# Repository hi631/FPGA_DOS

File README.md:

Build a DOS machine with FPGA.

Move "[next186](https://opencores.org/projects/next186_soc_pc)" on the board cut by CNC.
<br> Even if the software is existing and reliable, there is no guarantee that the hardware will work, so take the following steps.
<br> Step-1 Connect memory, IO, etc. to a commercially available FPGA (xc6lx9) board, move it with CP / M, and check the hardware operation.
<br> * Even with CP / M, the main memory is not static but DRAM.
<br> However, since burst access is not performed, defect verification is easy.
<br> Step-2 Operate as a DOS system on the above hardware.
<br> * Actually, the memory (DRAM) did not work properly, and I stepped on here for several months. How it works.
<br> Step-3 Create a printed circuit board with CNC, first verify the operation of the hardware with CP / M, and then operate the DOS system.
<br>
<br> Describe the hardware / software to be used for reference.
<br> [lx9-Step-1-io] Expansion platform used in Steps 1 and 2. It is operated by piercing a commercially available board (XC6SLX9 Mini Board).
<br> [MAIN-BOARD] Motherboard with FPGA and DRAM.
<br> [PMOD-IO] A board that connects the SD card and keyboard. Stick in MAIN-BOARD.
<br> [PMOD-VGA6] VGA display output. Stick in MAIN-BOARD.
<br> [lx9-Step1-CPM80] Circuit for operating CP / M (verilog)
<br> [lx9-Next186_SoC] Circuit for operating DOS (verilog)
<br>「[SD2G_Dos_F.zip] free MS-DOS SD-image

<br> For details, see "[Qiita](https://qiita.com/hi631/items/e8e0db06a52938b57632)".

<br>
<br> Part 2: I will run DOS using the CYC1000 board (cut-out edition)

<br> #Move on breadboard
<br> Just stab the CYC1000 into the breadboard and stab the IO in the same way. Only this.
<br> IO is a board, but there is no problem with wiring on the board.
<br> The wiring is the same as "[Board] ", so please refer to that.
<br> #Move with a compact board.
<br> A compact board with breadboard wiring cut by CNC. That's all.
<br> [Board made with eagle] max1000_eagle
<br> #soft
<br> The breadboard and board are the same software.
<br> However, I just changed the pin layout of next186.
<br> [Software to write to FPGA] max1000_Next186_SoC
<br> [Boot disk image] SD2G_Dos_F.zip

<br> For details, see "[Qiita](https://qiita.com/hi631/items/d948d38c25a411d28f2b)".

<br>DOSマシンをFPGAで作る。

<br>　「[next186](https://opencores.org/projects/next186_soc_pc)」をCNCで切削した基板上で動かす。
<br>　ソフトが既存で信頼できても、ハードが動作する保証は無いので、次のようなステップを踏む。
<br>　Step-1　市販FPGA(xc6lx9)基板にメモリ、IO等を繋ぎ、CP/Mで動かしハード動作を確認。
<br>　　　　　※CP/Mでも、メインメモリはスタティックでは無くDRAMで構成する。
<br>　　　　　　但し、バーストアクセスは行わないので、不具合検証はやり易い。
<br>　Step-2　上記ハード上で、DOSシステムとして動作させる。
<br>　　　　　※実際の所、メモリ(DRAM)が正常に動作せず、ここで数か月足踏みした。しくしく。
<br>　Step-3　CNCでプリント基板を作成し、先にCP/Mでハードの動作検証を行い、その後DOSシステムを動作させる。
<br>
<br>　使用するハード/ソフトを参考まで記載。
<br>　　[lx9-Step-1-io]　　Step-1,2で使用する拡張基盤。市販基板(XC6SLX9 Mini Board)に刺して動作させる。
<br>
<br>　　[MAIN-BOARD]　FPGAとDRAMを乗せた基盤。
<br>
<br>　　[PMOD-IO]　　SDカードとキーボードを繋ぐ基板。MAIN-BOARDに刺す。
<br>　　[PMOD-VGA6]　VGAディスプレイ出力。MAIN-BOARDに刺す。
<br>
<br>　　[lx9-Step1-CPM80]　CP/Mを動作させる為の回路(verilog)
<br>　　[lx9-Next186_SoC]　DOSを動作させるための回路(verilog)
<br>「[SD2G_Dos_F.zip](https://github.com/hi631/FPGA_DOS/blob/master/SD2G_Dos_F.zip)　free MS-DOS SDイメージ

<br>詳細は　「[Ｑｉｉｔａ](https://qiita.com/hi631/items/e8e0db06a52938b57632)」を見てください。

<br>その２：CYC1000ボードを使ってDOSを動かすぞ(手抜き編)
　
<br>#ブレッドボード上で動かす
<br>　CYC1000をブレッドボードに刺し、同様にＩＯを刺すだけ。これだけです。
<br>　ＩＯは基板にしたが、ボード上で配線でもなんら問題ない。
<br>　配線は「[基板]((https://github.com/hi631/FPGA_DOS/tree/master/max1000_eagle))」と同じなので、そちらを参照してね。
<br>

<br>#コンパクトな基板で動かす。
<br>　ブレッドボードの配線を、CNCで切削したコンパクトな基板。それだけです。
<br>　[eagleで作製した基板](https://github.com/hi631/FPGA_DOS/tree/master/max1000_eagle)
<br>

<br>#ソフト
<br>　ブレッドボード、基板共に同一ソフトです。
<br>　と言っても、next186のピン配置を変えただけですが。
<br>　[ＦＰＧＡに書き込むソフト](https://github.com/hi631/FPGA_DOS/tree/master/max1000_Next186_SoC)
<br>　[ブートディスクのイメージ](https://github.com/hi631/FPGA_DOS/blob/master/SD2G_Dos_F.zip)

<br>詳細は　「[Ｑｉｉｔａ](https://qiita.com/hi631/items/d948d38c25a411d28f2b)」を見てください。

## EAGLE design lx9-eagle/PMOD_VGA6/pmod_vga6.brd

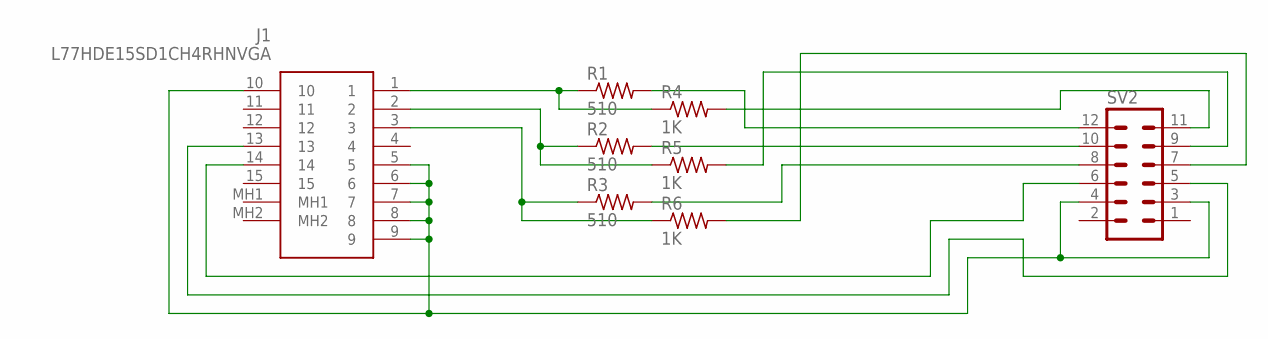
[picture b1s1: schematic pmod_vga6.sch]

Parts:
J1: L77HDE15SD1CH4RHNVGA
R1, R2, R3: 510; R0805
R4, R5, R6: 1K; R0805
SV2: MA06-2

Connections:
unnamed: J1.1, R1.1, R4.1
unnamed: J1.2, R2.1, R5.1
unnamed: J1.3, R3.1, R6.1
unnamed: R1.2, SV2.12
unnamed: R4.2, SV2.11
unnamed: R2.2, SV2.10
unnamed: R5.2, SV2.9
unnamed: R3.2, SV2.8
unnamed: R6.2, SV2.7
unnamed: J1.14, SV2.6
unnamed: J1.13, SV2.5
unnamed: J1.5, J1.6, J1.7, J1.8, J1.9, J1.10, SV2.3, SV2.4

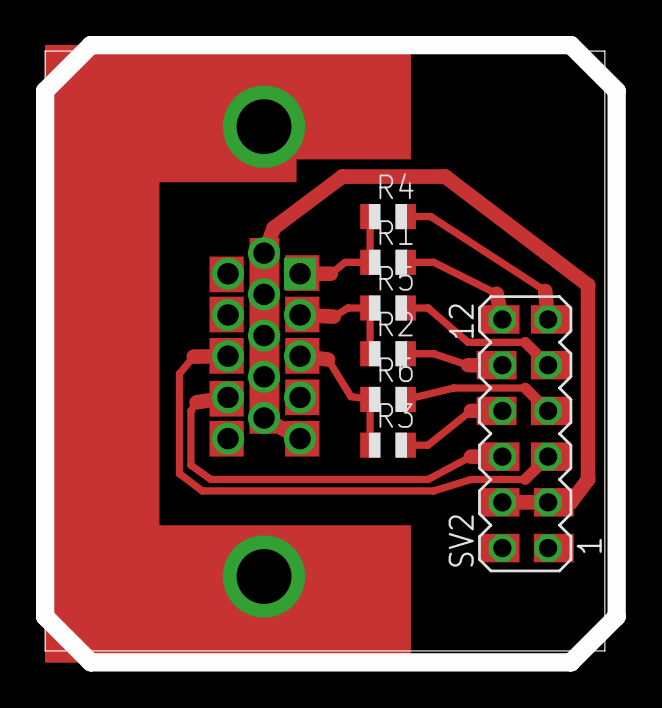
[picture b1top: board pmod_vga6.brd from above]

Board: 2 copper layers, 31.8 x 34.3 mm, 8 parts (1 on the bottom side), 12 nets.

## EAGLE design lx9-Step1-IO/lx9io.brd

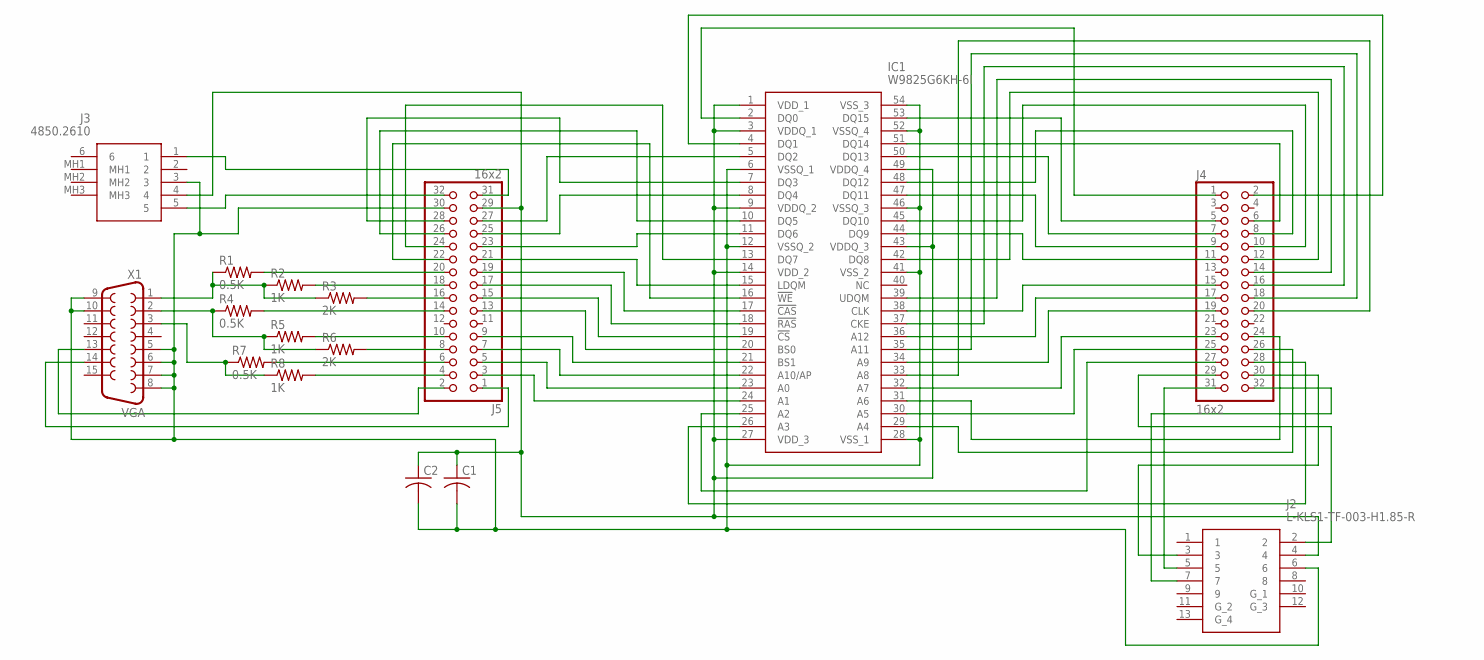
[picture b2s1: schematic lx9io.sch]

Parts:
C1, C2: C-USC0805; C0805
IC1: W9825G6KH-6I; SOP80P1176X120-54N
J2: L-KLS1-TF-003-H1.85-R
J3: 4850.2610; 48502610
J4, J5: 16x2; 2X16
R1, R4, R7: 0.5K; M0805
R2, R5, R8: 1K; M0805
R3, R6: 2K; M0805
X1: VGA; HDF15H

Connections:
unnamed: IC1.50 (DQ13), J4.7
unnamed: IC1.2 (DQ0), J4.1
unnamed: C1.2, C2.2, IC1.6 (VSSQ_1), IC1.12 (VSSQ_2), IC1.28 (VSS_1), IC1.41 (VSS_2), IC1.46 (VSSQ_3), IC1.52 (VSSQ_4), IC1.54 (VSS_3), J2.6, J3.3, J5.30, X1.5, X1.6, X1.7, X1.8, X1.9, X1.10
unnamed: IC1.53 (DQ15), J4.5
unnamed: IC1.47 (DQ11), J4.9
unnamed: IC1.44 (DQ9), J4.11
unnamed: IC1.38 (CLK), J4.15
unnamed: IC1.36 (A12), J4.17
unnamed: IC1.34 (A9), J4.19
unnamed: IC1.32 (A7), J4.23
unnamed: IC1.30 (A5), J4.25
unnamed: IC1.51 (DQ14), J4.6
unnamed: IC1.48 (DQ12), J4.8
unnamed: IC1.45 (DQ10), J4.10
unnamed: IC1.42 (DQ8), J4.12
unnamed: IC1.39 (UDQM), J4.14
unnamed: IC1.37 (CKE), J4.16
unnamed: IC1.35 (A11), J4.18
unnamed: IC1.33 (A8), J4.20
unnamed: IC1.31 (A6), J4.24
unnamed: IC1.29 (A4), J4.26
unnamed: IC1.4 (DQ1), J4.2
unnamed: IC1.25 (A2), J4.27
unnamed: IC1.26 (A3), J4.28
unnamed: IC1.10 (DQ5), J5.26
unnamed: IC1.5 (DQ2), J5.27
unnamed: IC1.7 (DQ3), J5.28
unnamed: IC1.8 (DQ4), J5.25
unnamed: IC1.11 (DQ6), J5.23
unnamed: IC1.13 (DQ7), J5.24
unnamed: IC1.15 (LDQM), J5.21
unnamed: IC1.16 (!WE), J5.22
unnamed: IC1.17 (!CAS), J5.19
unnamed: IC1.18 (!RAS), J5.17
unnamed: IC1.19 (!CS), J5.15
unnamed: IC1.20 (BS0), J5.13
unnamed: IC1.21 (BS1), J5.9
unnamed: IC1.22 (A10/AP), J5.7
unnamed: IC1.23 (A0), J5.5
unnamed: IC1.24 (A1), J5.3
unnamed: R1.1, R2.1, R3.1, X1.1
unnamed: R4.1, R5.1, R6.1, X1.2
unnamed: R7.1, R8.1, X1.3
unnamed: J5.20, R1.2
unnamed: J5.18, R2.2
unnamed: J5.16, R3.2
unnamed: J5.14, R4.2
unnamed: J5.10, R5.2
unnamed: J5.8, R6.2
unnamed: J5.6, R7.2
unnamed: J5.4, R8.2
unnamed: J5.1, X1.14
unnamed: J3.1, J5.31
unnamed: J3.5, J5.32
unnamed: J5.2, X1.13
unnamed: C1.1, C2.1, IC1.1 (VDD_1), IC1.3 (VDDQ_1), IC1.9 (VDDQ_2), IC1.14 (VDD_2), IC1.27 (VDD_3), IC1.43 (VDDQ_3), IC1.49 (VDDQ_4), J2.4, J3.4, J5.29
unnamed: J2.5, J4.31
unnamed: J2.7, J4.32
unnamed: J2.2, J4.29
unnamed: J2.3, J4.30

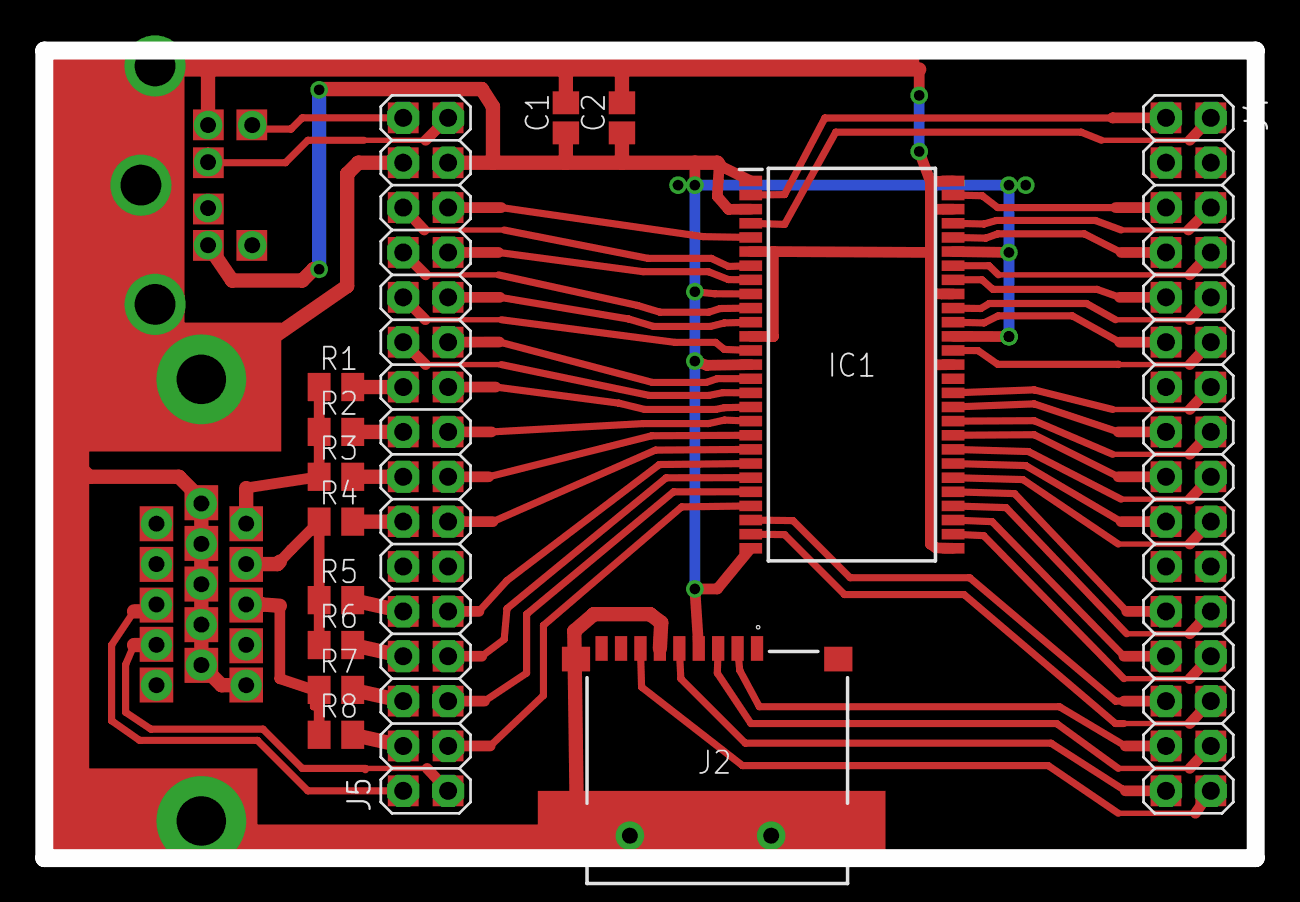
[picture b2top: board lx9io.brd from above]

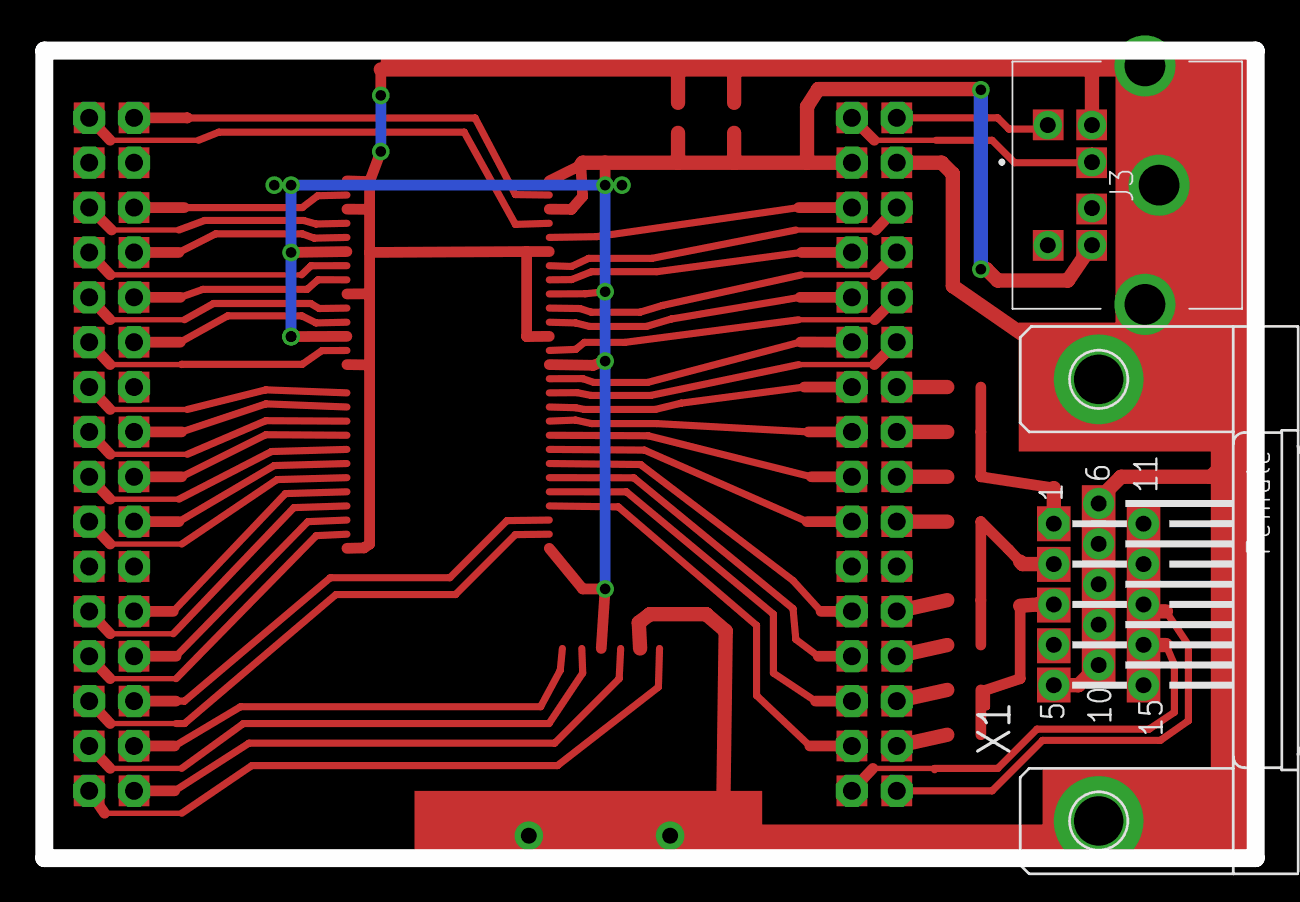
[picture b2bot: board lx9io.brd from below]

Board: 2 copper layers, 68.6 x 45.7 mm, 16 parts (2 on the bottom side), 60 nets.

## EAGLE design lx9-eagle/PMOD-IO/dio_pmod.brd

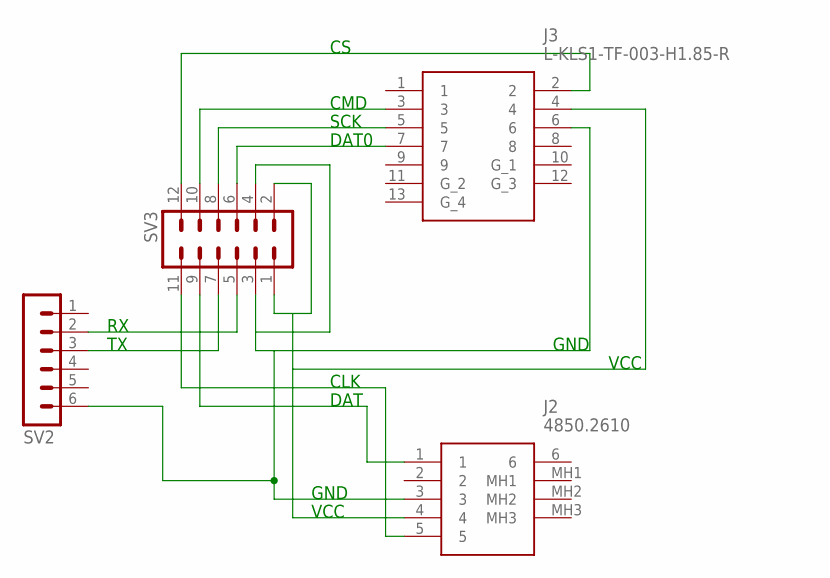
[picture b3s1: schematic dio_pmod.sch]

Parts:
J2: 4850.2610; 48502610
J3: L-KLS1-TF-003-H1.85-R
SV2: MA06-1
SV3: MA06-2

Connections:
GND: J2.3, J3.6, SV2.6, SV3.3, SV3.4
unnamed: SV2.2, SV3.5
unnamed: SV2.3, SV3.7
unnamed: J2.1, SV3.9
unnamed: J3.5, SV3.8
unnamed: J3.3, SV3.10
unnamed: J3.7, SV3.6
unnamed: J2.5, SV3.11
unnamed: J3.2, SV3.12
VCC: J2.4, J3.4, SV3.1, SV3.2

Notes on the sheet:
GND
VCC
CMD
SCK
DAT0
CLK
DAT

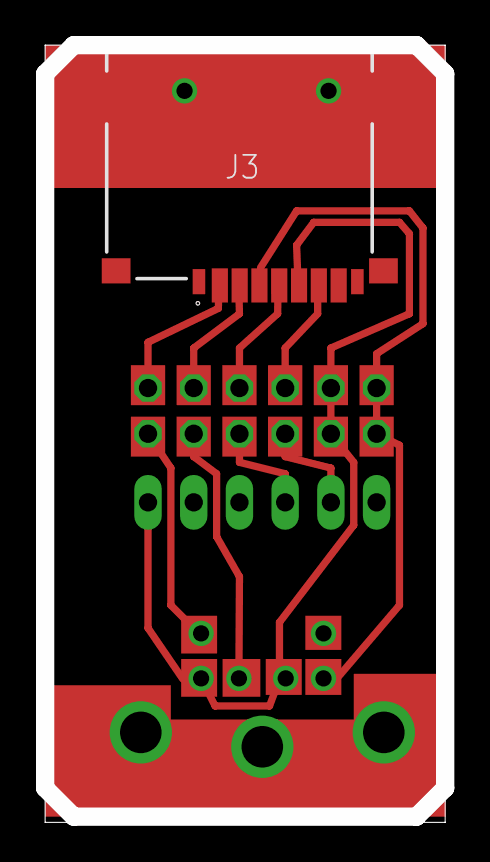
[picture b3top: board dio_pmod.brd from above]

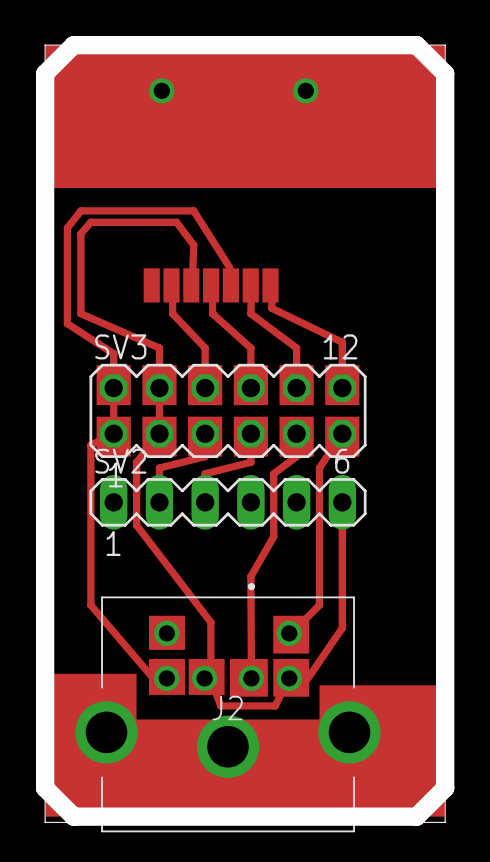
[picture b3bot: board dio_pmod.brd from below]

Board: 2 copper layers, 22.2 x 43.2 mm, 4 parts (3 on the bottom side), 10 nets.

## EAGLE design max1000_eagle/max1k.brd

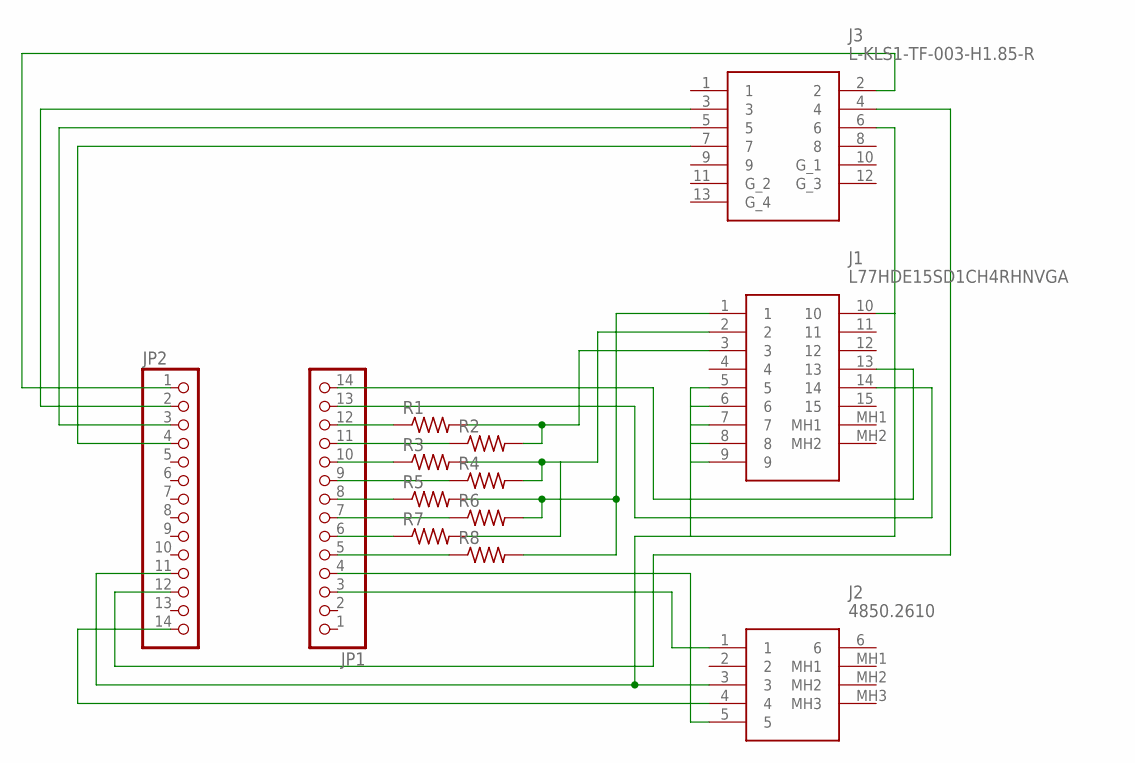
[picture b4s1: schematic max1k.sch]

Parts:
J1: L77HDE15SD1CH4RHNVGA
J2: 4850.2610; 48502610
J3: L-KLS1-TF-003-H1.85-R
JP1, JP2: PINHD-1X14-CB; 1X14-CB
R1, R2, R3, R4, R5, R6, R7, R8: R-US_R0805; R0805

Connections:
GND: J1.5, J1.6, J1.7, J1.8, J1.9, J1.10, J2.3, J3.6, JP2.11
unnamed: J1.13, JP1.14
unnamed: J1.14, JP1.13
unnamed: JP1.12, R1.1
unnamed: JP1.11, R2.1
unnamed: JP1.10, R3.1
unnamed: JP1.9, R4.1
unnamed: JP1.8, R5.1
unnamed: JP1.7, R6.1
unnamed: JP1.6, R7.1
unnamed: JP1.5, R8.1
unnamed: J1.3, R1.2, R2.2
unnamed: J1.2, R3.2, R4.2, R7.2
unnamed: J1.1, R5.2, R6.2, R8.2
unnamed: J3.4, JP2.12
unnamed: J2.4, JP2.14
unnamed: J2.1, JP1.3
unnamed: J3.5, JP2.3
unnamed: J3.3, JP2.2
unnamed: J3.7, JP2.4
unnamed: J2.5, JP1.4
unnamed: J3.2, JP2.1

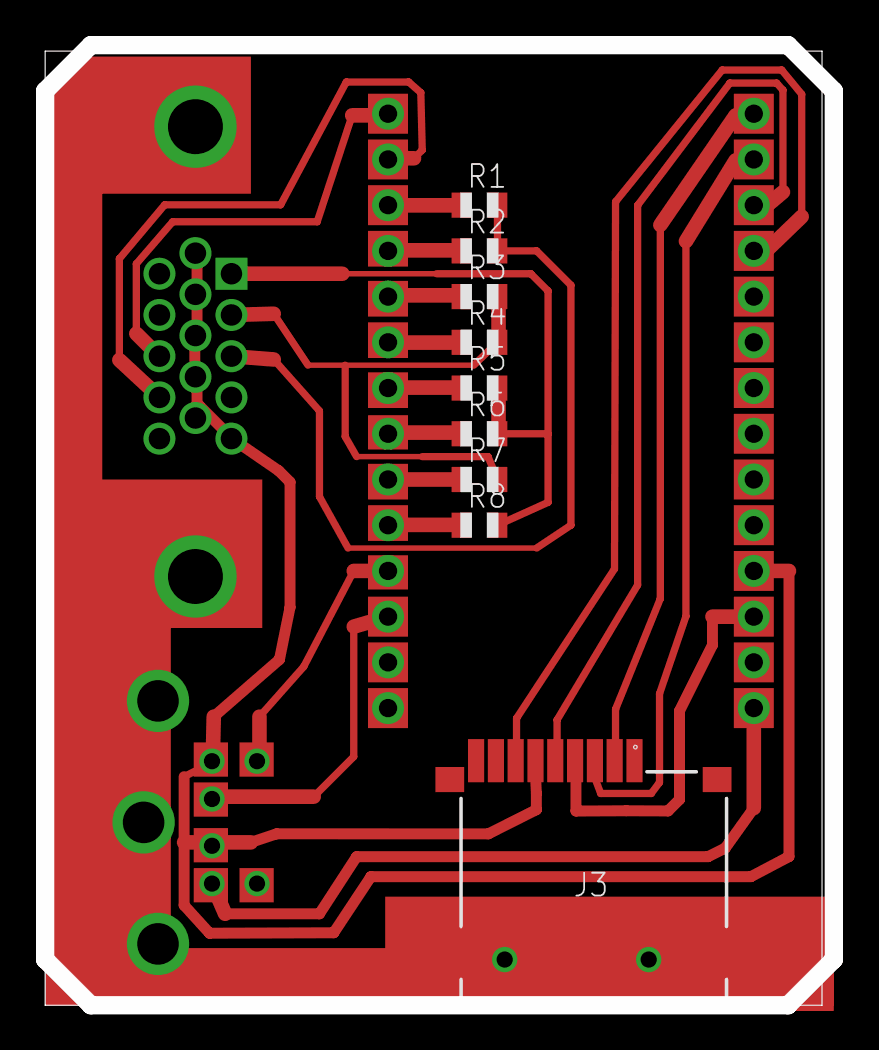
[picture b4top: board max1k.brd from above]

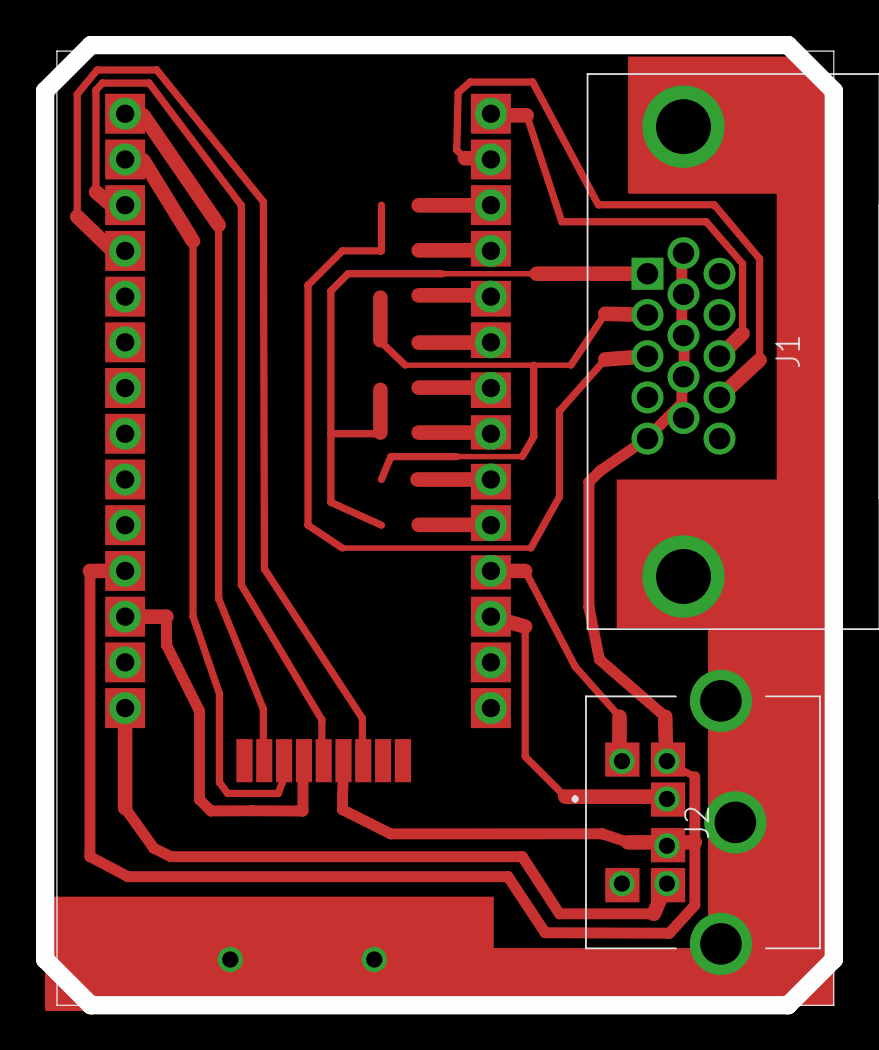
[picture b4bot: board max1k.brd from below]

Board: 2 copper layers, 43.8 x 53.3 mm, 13 parts (2 on the bottom side), 22 nets.

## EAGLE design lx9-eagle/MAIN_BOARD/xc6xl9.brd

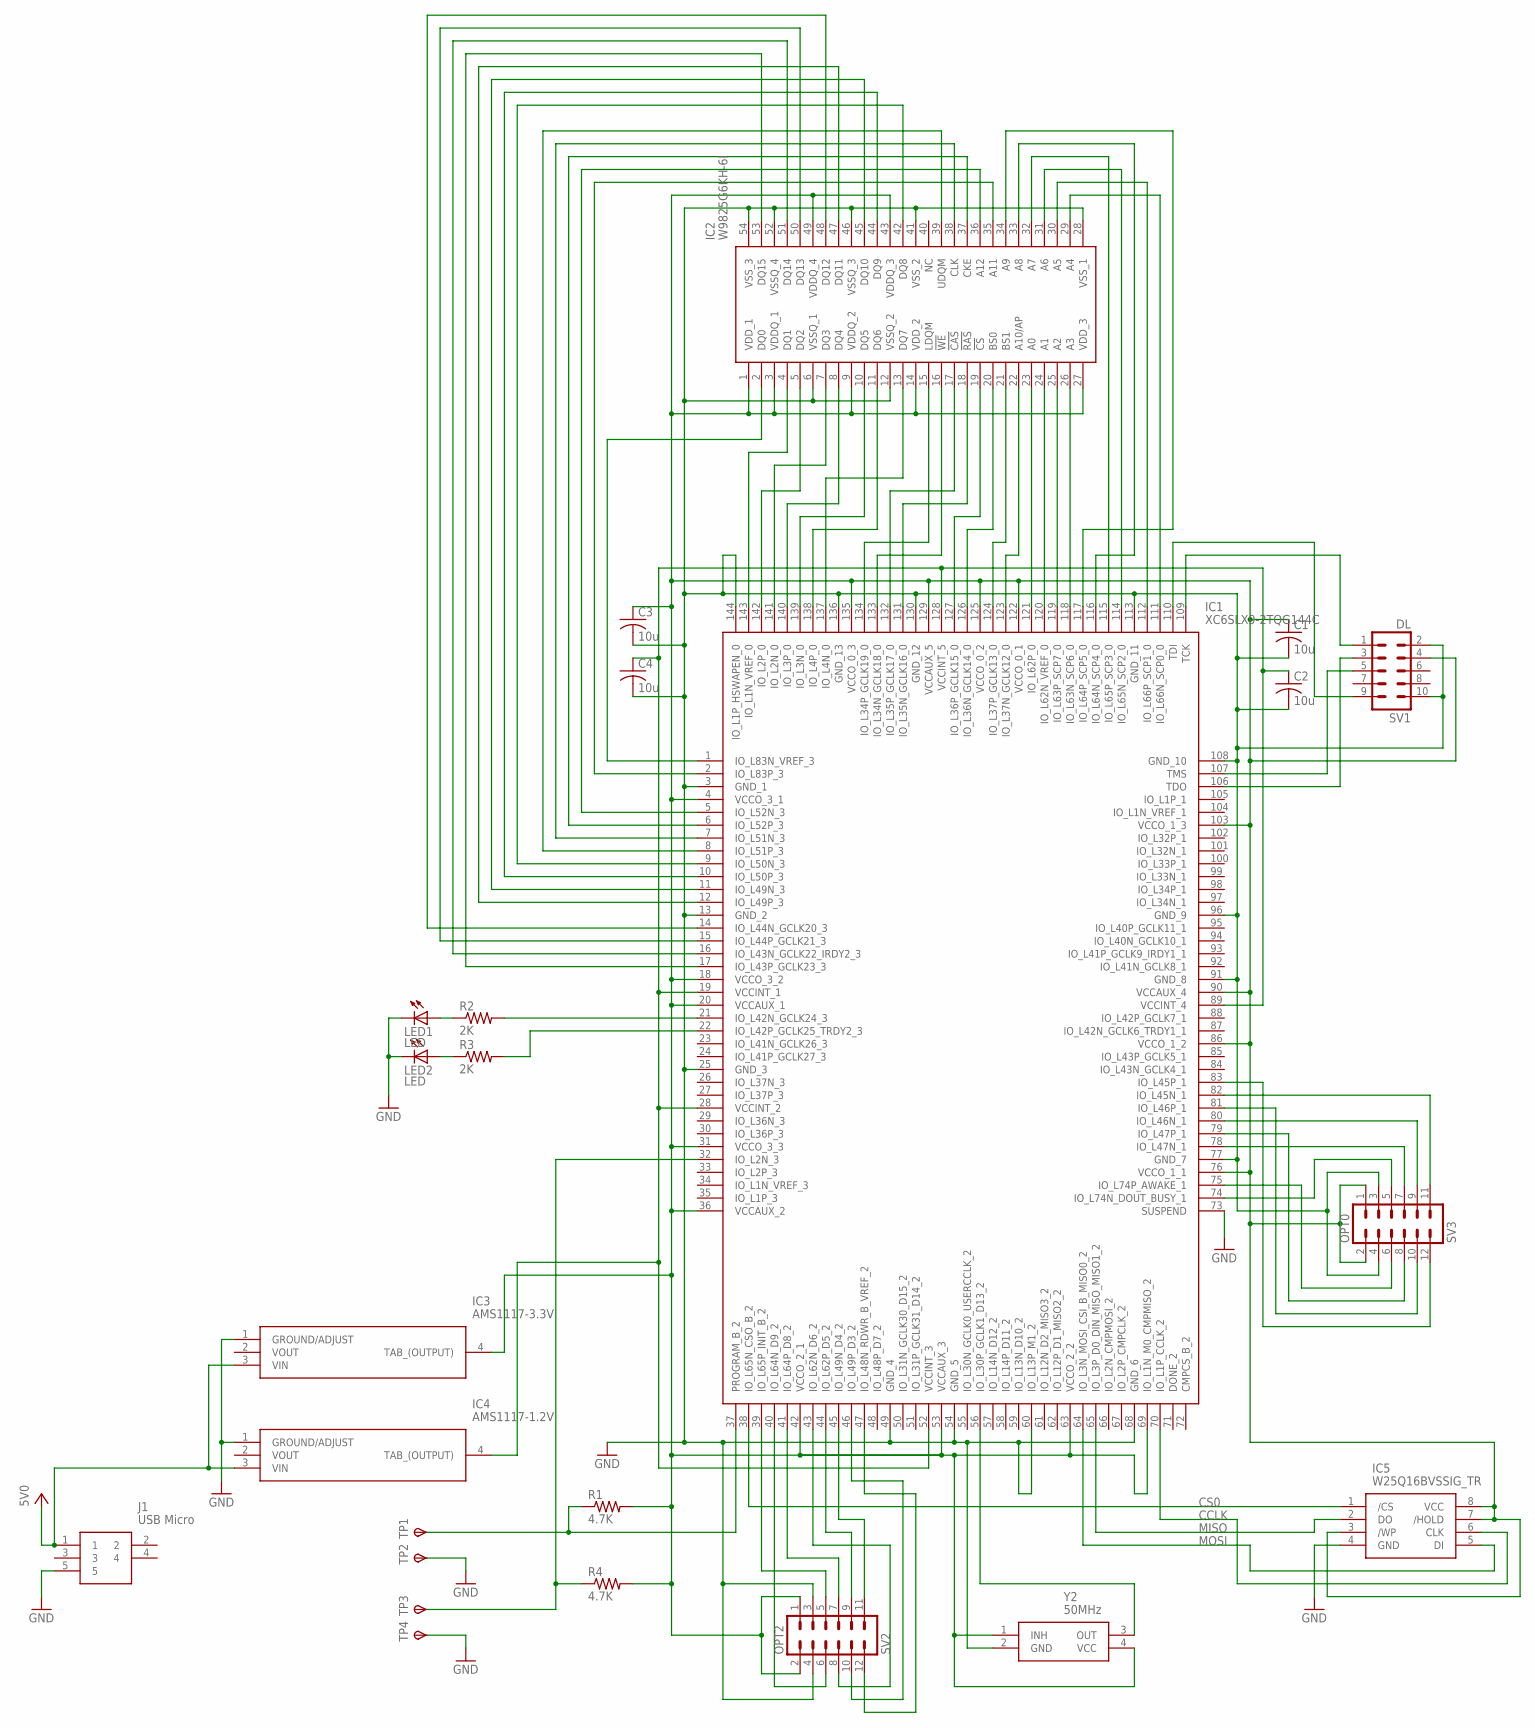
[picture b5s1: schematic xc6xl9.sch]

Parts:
C1, C2, C3, C4: 10u; C0805K
IC1: XC6SLX9-2TQG144C; QFP50P2200X2200X160-144N
IC2: W9825G6KH-6I; SOP80P1176X120-54N
IC3: AMS1117-3.3V; SOT229P700X180-4N
IC4: AMS1117-1.2V; SOT229P700X180-4N
IC5: W25Q16BVSSIG_TR; SOIC127P790X216-8N
J1: USB Micro; 10104110-0001LF
LED1, LED2: LED; CHIPLED_0805
R1, R4: 4.7K; R0805
R2, R3: 2K; R0805
SV1: DL; MA05-2
SV2: OPT2; MA06-2
SV3: OPT0; MA06-2
TP1, TP2, TP3, TP4: TPSTP10SQ; TP10SQ
Y2: 50MHz; KC5032A12.0000CM0E00

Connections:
3V3: C1.1, C3.1, IC1.4 (VCCO_3_1), IC1.18 (VCCO_3_2), IC1.20 (VCCAUX_1), IC1.31 (VCCO_3_3), IC1.36 (VCCAUX_2), IC1.42 (VCCO_2_1), IC1.53 (VCCAUX_3), IC1.63 (VCCO_2_2), IC1.69 (IO_L1N_M0_CMPMISO_2), IC1.76 (VCCO_1_1), IC1.86 (VCCO_1_2), IC1.90 (VCCAUX_4), IC1.103 (VCCO_1_3), IC1.122 (VCCO_0_1), IC1.125 (VCCO_0_2), IC1.129 (VCCAUX_5), IC1.135 (VCCO_0_3), IC2.1 (VDD_1), IC2.3 (VDDQ_1), IC2.9 (VDDQ_2), IC2.14 (VDD_2), IC2.27 (VDD_3), IC2.43 (VDDQ_3), IC2.49 (VDDQ_4), IC3.4 (TAB_(OUTPUT)), IC5.3 (/WP), IC5.7 (/HOLD), IC5.8 (VCC), R1.2, R4.2, SV1.4, SV2.1, SV2.2, SV3.1, SV3.2, Y2.1 (INH), Y2.4 (VCC)
CCLK: IC1.70 (IO_L1P_CCLK_2), IC5.6 (CLK)
CS0: IC1.38 (IO_L65N_CSO_B_2), IC5.1 (/CS)
GND: C1.2, C2.2, C3.2, C4.2, IC1.3 (GND_1), IC1.13 (GND_2), IC1.25 (GND_3), IC1.49 (GND_4), IC1.54 (GND_5), IC1.60 (IO_L13P_M1_2), IC1.68 (GND_6), IC1.73 (SUSPEND), IC1.77 (GND_7), IC1.91 (GND_8), IC1.96 (GND_9), IC1.108 (GND_10), IC1.113 (GND_11), IC1.130 (GND_12), IC1.136 (GND_13), IC1.144 (IO_L1P_HSWAPEN_0), IC2.6 (VSSQ_1), IC2.12 (VSSQ_2), IC2.28 (VSS_1), IC2.41 (VSS_2), IC2.46 (VSSQ_3), IC2.52 (VSSQ_4), IC2.54 (VSS_3), IC3.1 (GROUND/ADJUST), IC4.1 (GROUND/ADJUST), IC5.4 (GND), J1.5, LED1.C, LED2.C, SV1.2, SV1.10, SV2.3, SV2.4, SV3.3, SV3.4, TP2.TP, TP4.TP, Y2.2 (GND)
MISO: IC1.65 (IO_L3P_D0_DIN_MISO_MISO1_2), IC5.2 (DO)
MOSI: IC1.64 (IO_L3N_MOSI_CSI_B_MISO0_2), IC5.5 (DI)
unnamed: IC1.56 (IO_L30P_GCLK1_D13_2), Y2.3 (OUT)
unnamed: IC1.109 (TCK), SV1.1
unnamed: IC1.106 (TDO), SV1.3
unnamed: IC1.107 (TMS), SV1.5
unnamed: IC1.110 (TDI), SV1.9
unnamed: IC1.111 (IO_L66N_SCP0_0), IC2.29 (A4)
unnamed: IC1.112 (IO_L66P_SCP1_0), IC2.30 (A5)
unnamed: IC1.114 (IO_L65N_SCP2_0), IC2.31 (A6)
unnamed: IC1.115 (IO_L65P_SCP3_0), IC2.32 (A7)
unnamed: IC1.116 (IO_L64N_SCP4_0), IC2.33 (A8)
unnamed: IC1.21 (IO_L42N_GCLK24_3), R2.2
unnamed: IC1.22 (IO_L42P_GCLK25_TRDY2_3), R3.2
unnamed: LED2.A, R3.1
unnamed: LED1.A, R2.1
unnamed: IC1.117 (IO_L64P_SCP5_0), IC2.34 (A9)
unnamed: IC1.118 (IO_L63N_SCP6_0), IC2.26 (A3)
unnamed: IC1.119 (IO_L63P_SCP7_0), IC2.25 (A2)
unnamed: IC1.120 (IO_L62N_VREF_0), IC2.24 (A1)
unnamed: IC1.121 (IO_L62P_0), IC2.23 (A0)
unnamed: IC1.123 (IO_L37N_GCLK12_0), IC2.22 (A10/AP)
unnamed: IC1.37 (PROGRAM_B_2), R1.1, TP1.TP
unnamed: IC1.124 (IO_L37P_GCLK13_0), IC2.21 (BS1)
unnamed: IC1.126 (IO_L36N_GCLK14_0), IC2.20 (BS0)
unnamed: IC1.127 (IO_L36P_GCLK15_0), IC2.19 (!CS)
unnamed: IC1.131 (IO_L35N_GCLK16_0), IC2.18 (!RAS)
unnamed: IC1.132 (IO_L35P_GCLK17_0), IC2.17 (!CAS)
unnamed: IC1.133 (IO_L34N_GCLK18_0), IC2.16 (!WE)
unnamed: IC1.134 (IO_L34P_GCLK19_0), IC2.15 (LDQM)
unnamed: IC1.137 (IO_L4N_0), IC2.13 (DQ7)
unnamed: IC1.138 (IO_L4P_0), IC2.11 (DQ6)
unnamed: IC1.139 (IO_L3N_0), IC2.10 (DQ5)
unnamed: IC1.140 (IO_L3P_0), IC2.8 (DQ4)
unnamed: IC1.141 (IO_L2N_0), IC2.7 (DQ3)
unnamed: IC1.142 (IO_L2P_0), IC2.5 (DQ2)
unnamed: IC1.143 (IO_L1N_VREF_0), IC2.4 (DQ1)
unnamed: IC1.2 (IO_L83P_3), IC2.35 (A11)
unnamed: IC1.5 (IO_L52N_3), IC2.36 (A12)
unnamed: IC1.6 (IO_L52P_3), IC2.37 (CKE)
unnamed: IC1.7 (IO_L51N_3), IC2.38 (CLK)
unnamed: IC1.8 (IO_L51P_3), IC2.39 (UDQM)
unnamed: IC1.32 (IO_L2N_3), R4.1, TP3.TP
unnamed: IC1.9 (IO_L50N_3), IC2.42 (DQ8)
unnamed: IC1.10 (IO_L50P_3), IC2.44 (DQ9)
unnamed: IC1.11 (IO_L49N_3), IC2.45 (DQ10)
unnamed: IC1.12 (IO_L49P_3), IC2.47 (DQ11)
unnamed: IC1.17 (IO_L43P_GCLK23_3), IC2.53 (DQ15)
unnamed: IC1.16 (IO_L43N_GCLK22_IRDY2_3), IC2.51 (DQ14)
unnamed: IC1.15 (IO_L44P_GCLK21_3), IC2.50 (DQ13)
unnamed: IC1.14 (IO_L44N_GCLK20_3), IC2.48 (DQ12)
unnamed: IC1.74 (IO_L74N_DOUT_BUSY_1), SV3.5
unnamed: IC1.75 (IO_L74P_AWAKE_1), SV3.6
unnamed: IC1.78 (IO_L47N_1), SV3.7
unnamed: IC1.79 (IO_L47P_1), SV3.8
unnamed: IC1.80 (IO_L46N_1), SV3.9
unnamed: IC1.82 (IO_L45N_1), SV3.11
unnamed: IC1.81 (IO_L46P_1), SV3.10
unnamed: IC1.83 (IO_L45P_1), SV3.12
unnamed: IC1.39 (IO_L65P_INIT_B_2), SV2.5
unnamed: IC1.40 (IO_L64N_D9_2), SV2.6
unnamed: IC1.41 (IO_L64P_D8_2), SV2.7
unnamed: IC1.43 (IO_L62N_D6_2), SV2.8
unnamed: IC1.44 (IO_L62P_D5_2), SV2.9
unnamed: IC1.46 (IO_L49P_D3_2), SV2.10
unnamed: IC1.45 (IO_L49N_D4_2), SV2.11
unnamed: IC1.47 (IO_L48N_RDWR_B_VREF_2), SV2.12
unnamed: IC1.1 (IO_L83N_VREF_3), IC2.2 (DQ0)
VCC: IC3.3 (VIN), IC4.3 (VIN), J1.1
VCCINT: C2.1, C4.1, IC1.19 (VCCINT_1), IC1.28 (VCCINT_2), IC1.52 (VCCINT_3), IC1.89 (VCCINT_4), IC1.128 (VCCINT_5), IC4.4 (TAB_(OUTPUT))

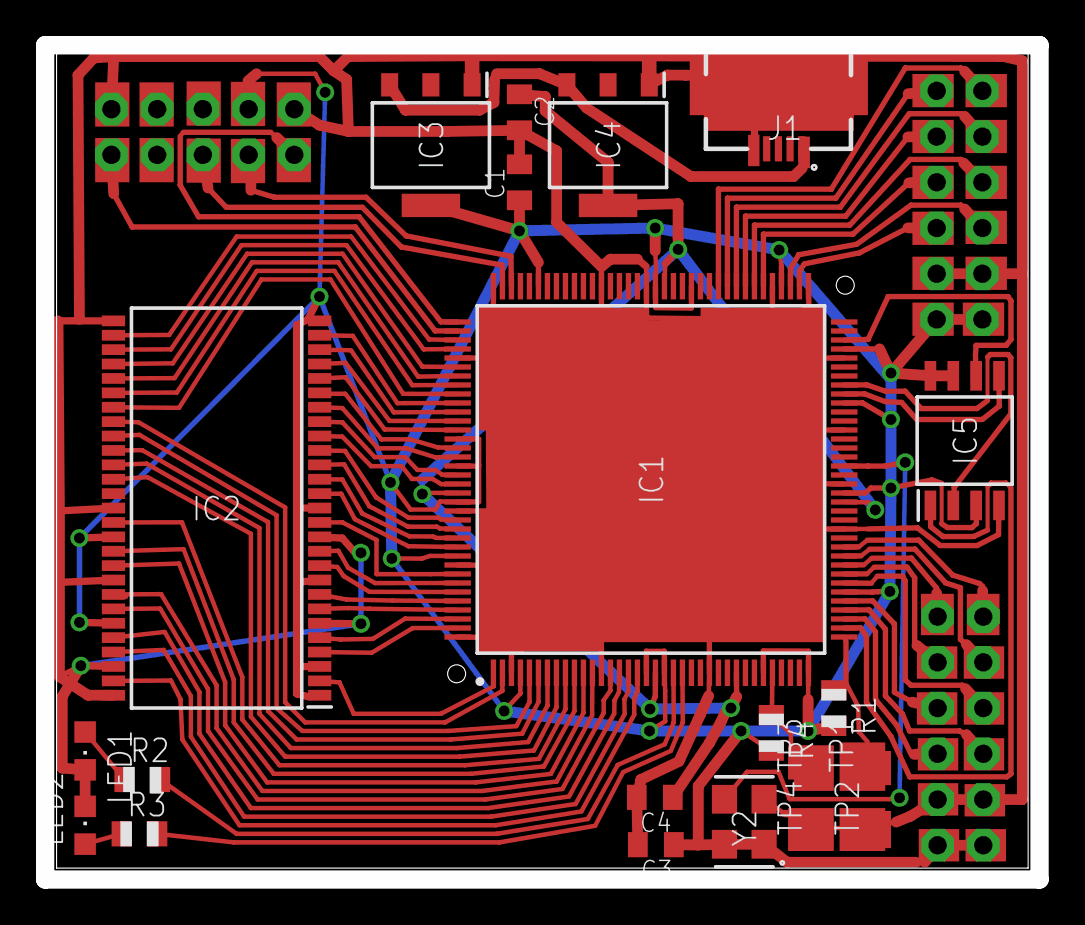
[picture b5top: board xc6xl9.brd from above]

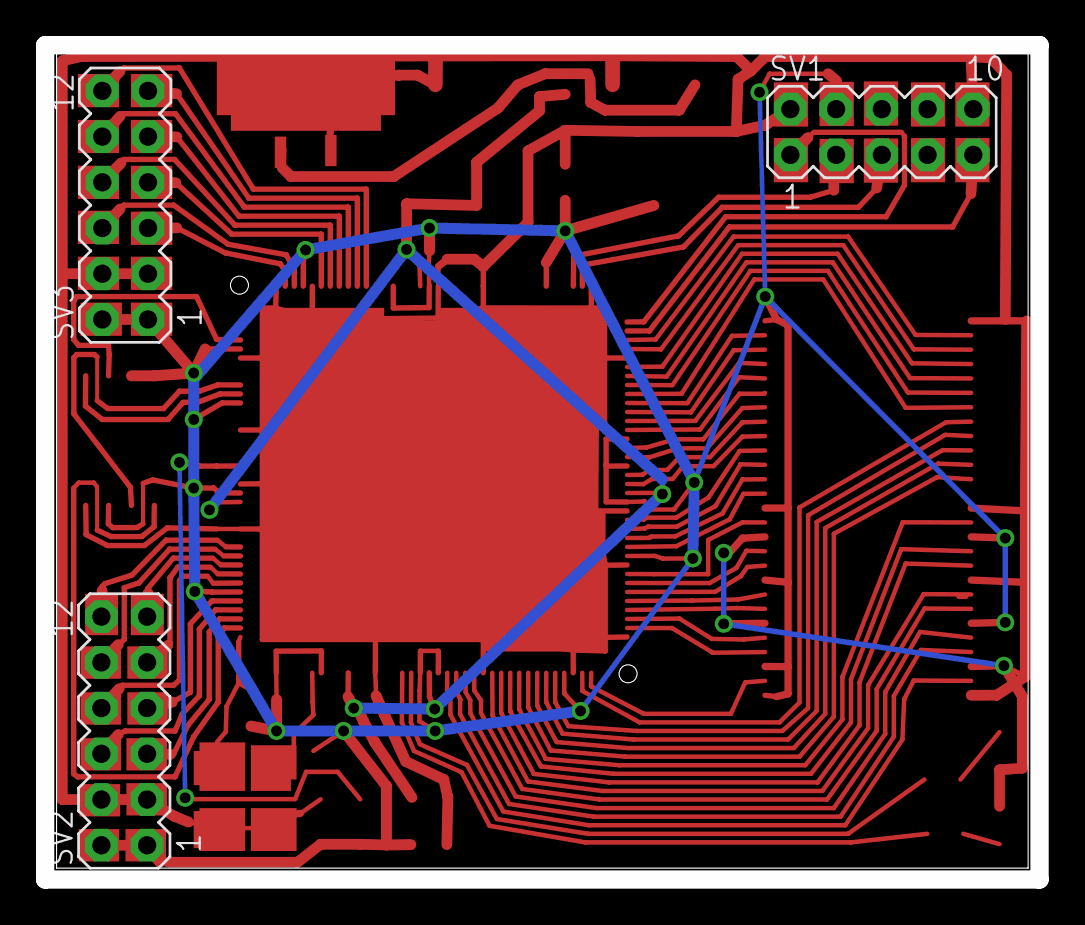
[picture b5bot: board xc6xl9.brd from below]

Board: 2 copper layers, 55.2 x 46.4 mm, 24 parts (3 on the bottom side), 74 nets.

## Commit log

2020-08-16 hatena
2020-08-17 modify
